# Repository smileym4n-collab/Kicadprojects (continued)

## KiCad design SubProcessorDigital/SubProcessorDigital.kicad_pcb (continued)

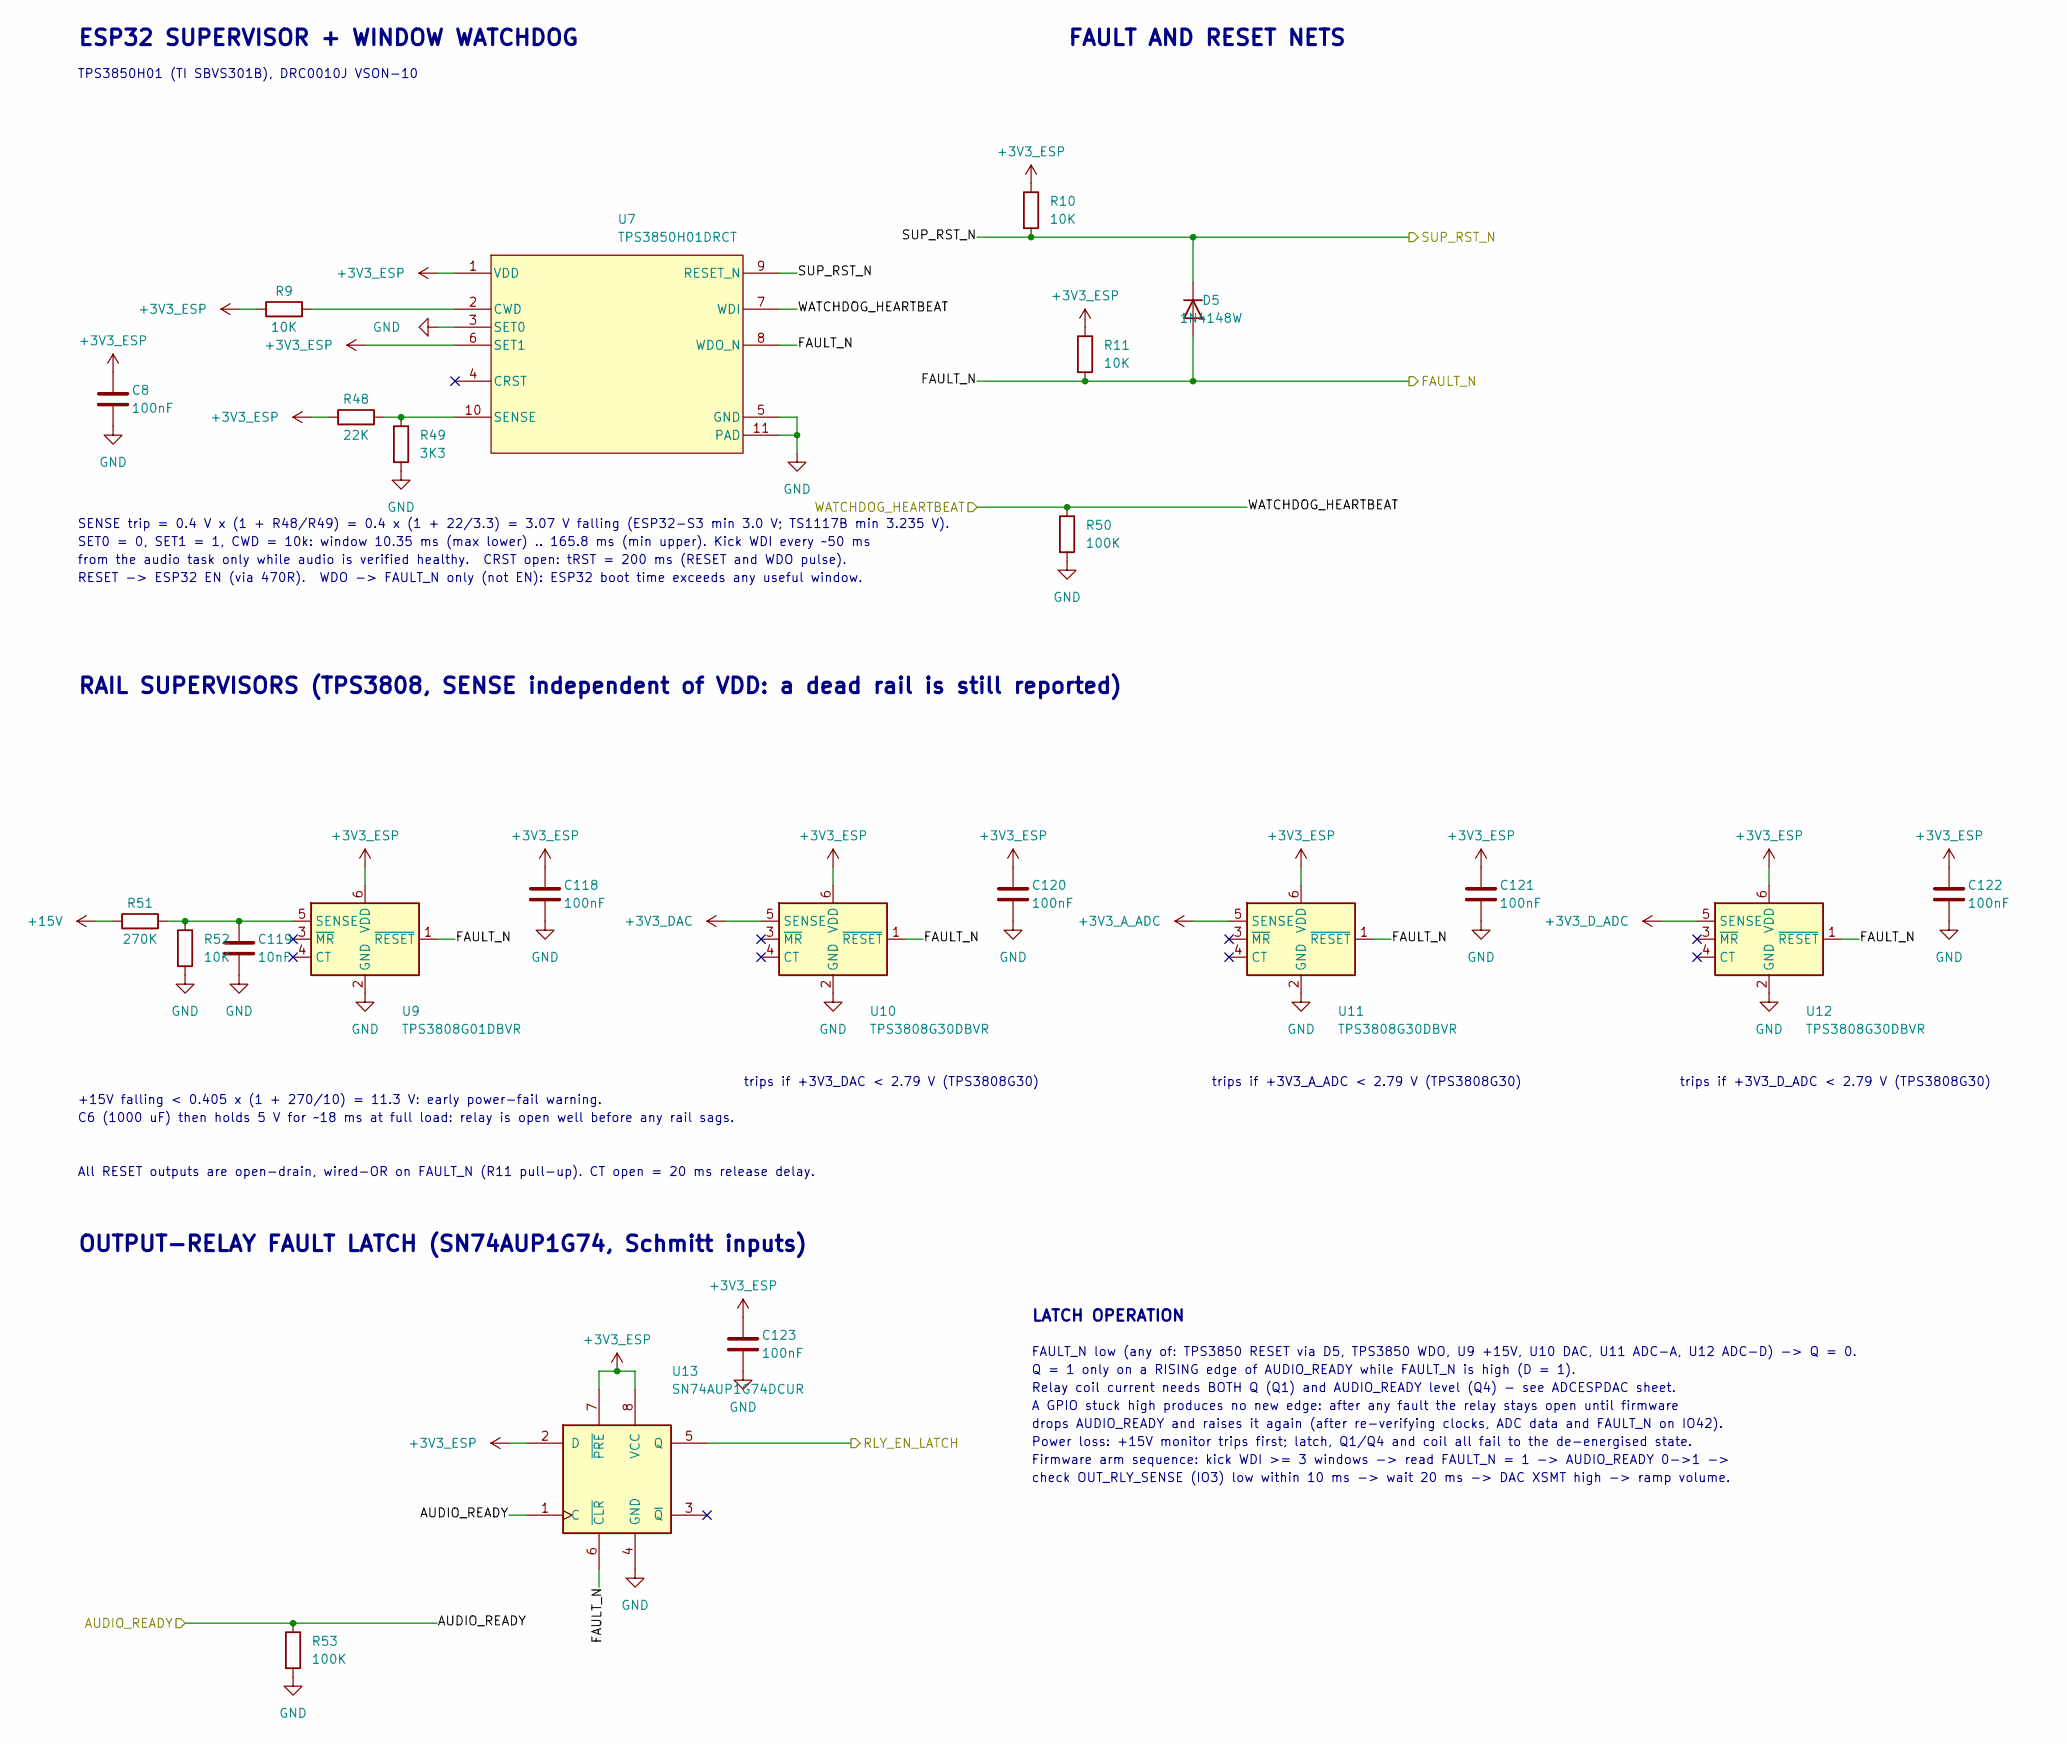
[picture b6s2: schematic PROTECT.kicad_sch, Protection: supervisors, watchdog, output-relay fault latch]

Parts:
C8, C118, C120, C121, C122, C123: 100nF; C_0603_1608Metric_Pad1.08x0.95mm_HandSolder; MPN Multicomp Pro MC0603B104K500CT (100nF 5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
C119: 10nF; C_0805_2012Metric_Pad1.18x1.45mm_HandSolder; MPN Walsin 0805B103K500CT (inventory)
D5: 1N4148W; D_SOD-123; MPN onsemi 1N4148W (inventory)
R9, R52: 10K; R_0805_2012Metric_Pad1.20x1.40mm_HandSolder; MPN 10k 0.1% thin film 2012 (inventory)
R10, R11: 10K; R_0805_2012Metric_Pad1.20x1.40mm_HandSolder; MPN KOA RK73B2ATTD103J (inventory)
R48: 22K; R_0805_2012Metric_Pad1.20x1.40mm_HandSolder; MPN Susumu RR1220P-223-D thin film 0.5% (in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
R49: 3K3; R_0805_2012Metric_Pad1.20x1.40mm_HandSolder; MPN Stackpole RMCF0805FT3K30 1% (inventory)
R50, R53: 100K; R_0805_2012Metric_Pad1.20x1.40mm_HandSolder; MPN Thick film 2012 (inventory)
R51: 270K; R_0805_2012Metric_Pad1.20x1.40mm_HandSolder; MPN 270k thick film 2012 (inventory)
U7: TPS3850H01DRCT; VSON-10-1EP_3x3mm_P0.5mm_EP1.65x2.4mm; MPN TPS3850H01DRCT
U9: TPS3808G01DBVR; SOT-23-6; MPN TPS3808G01DBVR
U10, U11, U12: TPS3808G30DBVR; SOT-23-6; MPN TPS3808G30DBVR
U13: SN74AUP1G74DCUR; VSSOP-8_2.3x2mm_P0.5mm; MPN SN74AUP1G74DCUR

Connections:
+3V3_A_ADC: U11.5 (SENSE); also elsewhere on the board
+3V3_DAC: U10.5 (SENSE); also elsewhere on the board
+3V3_D_ADC: U12.5 (SENSE); also elsewhere on the board
+3V3_ESP: C8.1, C118.1, C120.1, C121.1, C122.1, C123.1, R9.1, R10.1, R11.1, R48.1, U7.1 (VDD), U7.6 (SET1), U9.6 (VDD), U10.6 (VDD), U11.6 (VDD), U12.6 (VDD), U13.2 (D), U13.7 (~PRE), U13.8 (VCC); also elsewhere on the board
+15V: R51.1; also elsewhere on the board
/AUDIO_READY: R53.1, U13.1 (C); also elsewhere on the board
/FAULT_N: D5.2 (A), R11.2, U7.8 (WDO_N), U9.1 (~RESET), U10.1 (~RESET), U11.1 (~RESET), U12.1 (~RESET), U13.6 (~CLR); also elsewhere on the board
/RLY_EN_LATCH: U13.5 (Q); also elsewhere on the board
/SUP_RST_N: D5.1 (K), R10.2, U7.9 (RESET_N); also elsewhere on the board
/WATCHDOG_HEARTBEAT: R50.1, U7.7 (WDI); also elsewhere on the board
GND: C8.2, C118.2, C119.2, C120.2, C121.2, C122.2, C123.2, R49.2, R50.2, R52.2, R53.2, U7.3 (SET0), U7.5 (GND), U7.11 (PAD), U9.2 (GND), U10.2 (GND), U11.2 (GND), U12.2 (GND), U13.4 (GND); also elsewhere on the board
unnamed: R9.2, U7.2 (CWD)
unnamed: R48.2, R49.1, U7.10 (SENSE)
unnamed: C119.1, R51.2, R52.1, U9.5 (SENSE)

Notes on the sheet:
FAULT AND RESET NETS
ESP32 SUPERVISOR + WINDOW WATCHDOG
trips if +3V3_DAC < 2.79 V (TPS3808G30)
Relay coil current needs BOTH Q (Q1) and AUDIO_READY level (Q4) - see ADCESPDAC sheet.
Power loss: +15V monitor trips first; latch, Q1/Q4 and coil all fail to the de-energised state.
SENSE trip = 0.4 V x (1 + R48/R49) = 0.4 x (1 + 22/3.3) = 3.07 V falling (ESP32-S3 min 3.0 V; TS1117B min 3.235 V).
All RESET outputs are open-drain, wired-OR on FAULT_N (R11 pull-up). CT open = 20 ms release delay.
drops AUDIO_READY and raises it again (after re-verifying clocks, ADC data and FAULT_N on IO42).
RESET -> ESP32 EN (via 470R). WDO -> FAULT_N only (not EN): ESP32 boot time exceeds any useful window.
+15V falling < 0.405 x (1 + 270/10) = 11.3 V: early power-fail warning.
Q = 1 only on a RISING edge of AUDIO_READY while FAULT_N is high (D = 1).
Firmware arm sequence: kick WDI >= 3 windows -> read FAULT_N = 1 -> AUDIO_READY 0->1 ->
trips if +3V3_A_ADC < 2.79 V (TPS3808G30)
trips if +3V3_D_ADC < 2.79 V (TPS3808G30)
OUTPUT-RELAY FAULT LATCH (SN74AUP1G74, Schmitt inputs)
A GPIO stuck high produces no new edge: after any fault the relay stays open until firmware
TPS3850H01 (TI SBVS301B), DRC0010J VSON-10
LATCH OPERATION
from the audio task only while audio is verified healthy. CRST open: tRST = 200 ms (RESET and WDO pulse).
C6 (1000 uF) then holds 5 V for ~18 ms at full load: relay is open well before any rail sags.
check OUT_RLY_SENSE (IO3) low within 10 ms -> wait 20 ms -> DAC XSMT high -> ramp volume.
SET0 = 0, SET1 = 1, CWD = 10k: window 10.35 ms (max lower) .. 165.8 ms (min upper). Kick WDI every ~50 ms
FAULT_N low (any of: TPS3850 RESET via D5, TPS3850 WDO, U9 +15V, U10 DAC, U11 ADC-A, U12 ADC-D) -> Q = 0.
RAIL SUPERVISORS (TPS3808, SENSE independent of VDD: a dead rail is still reported)

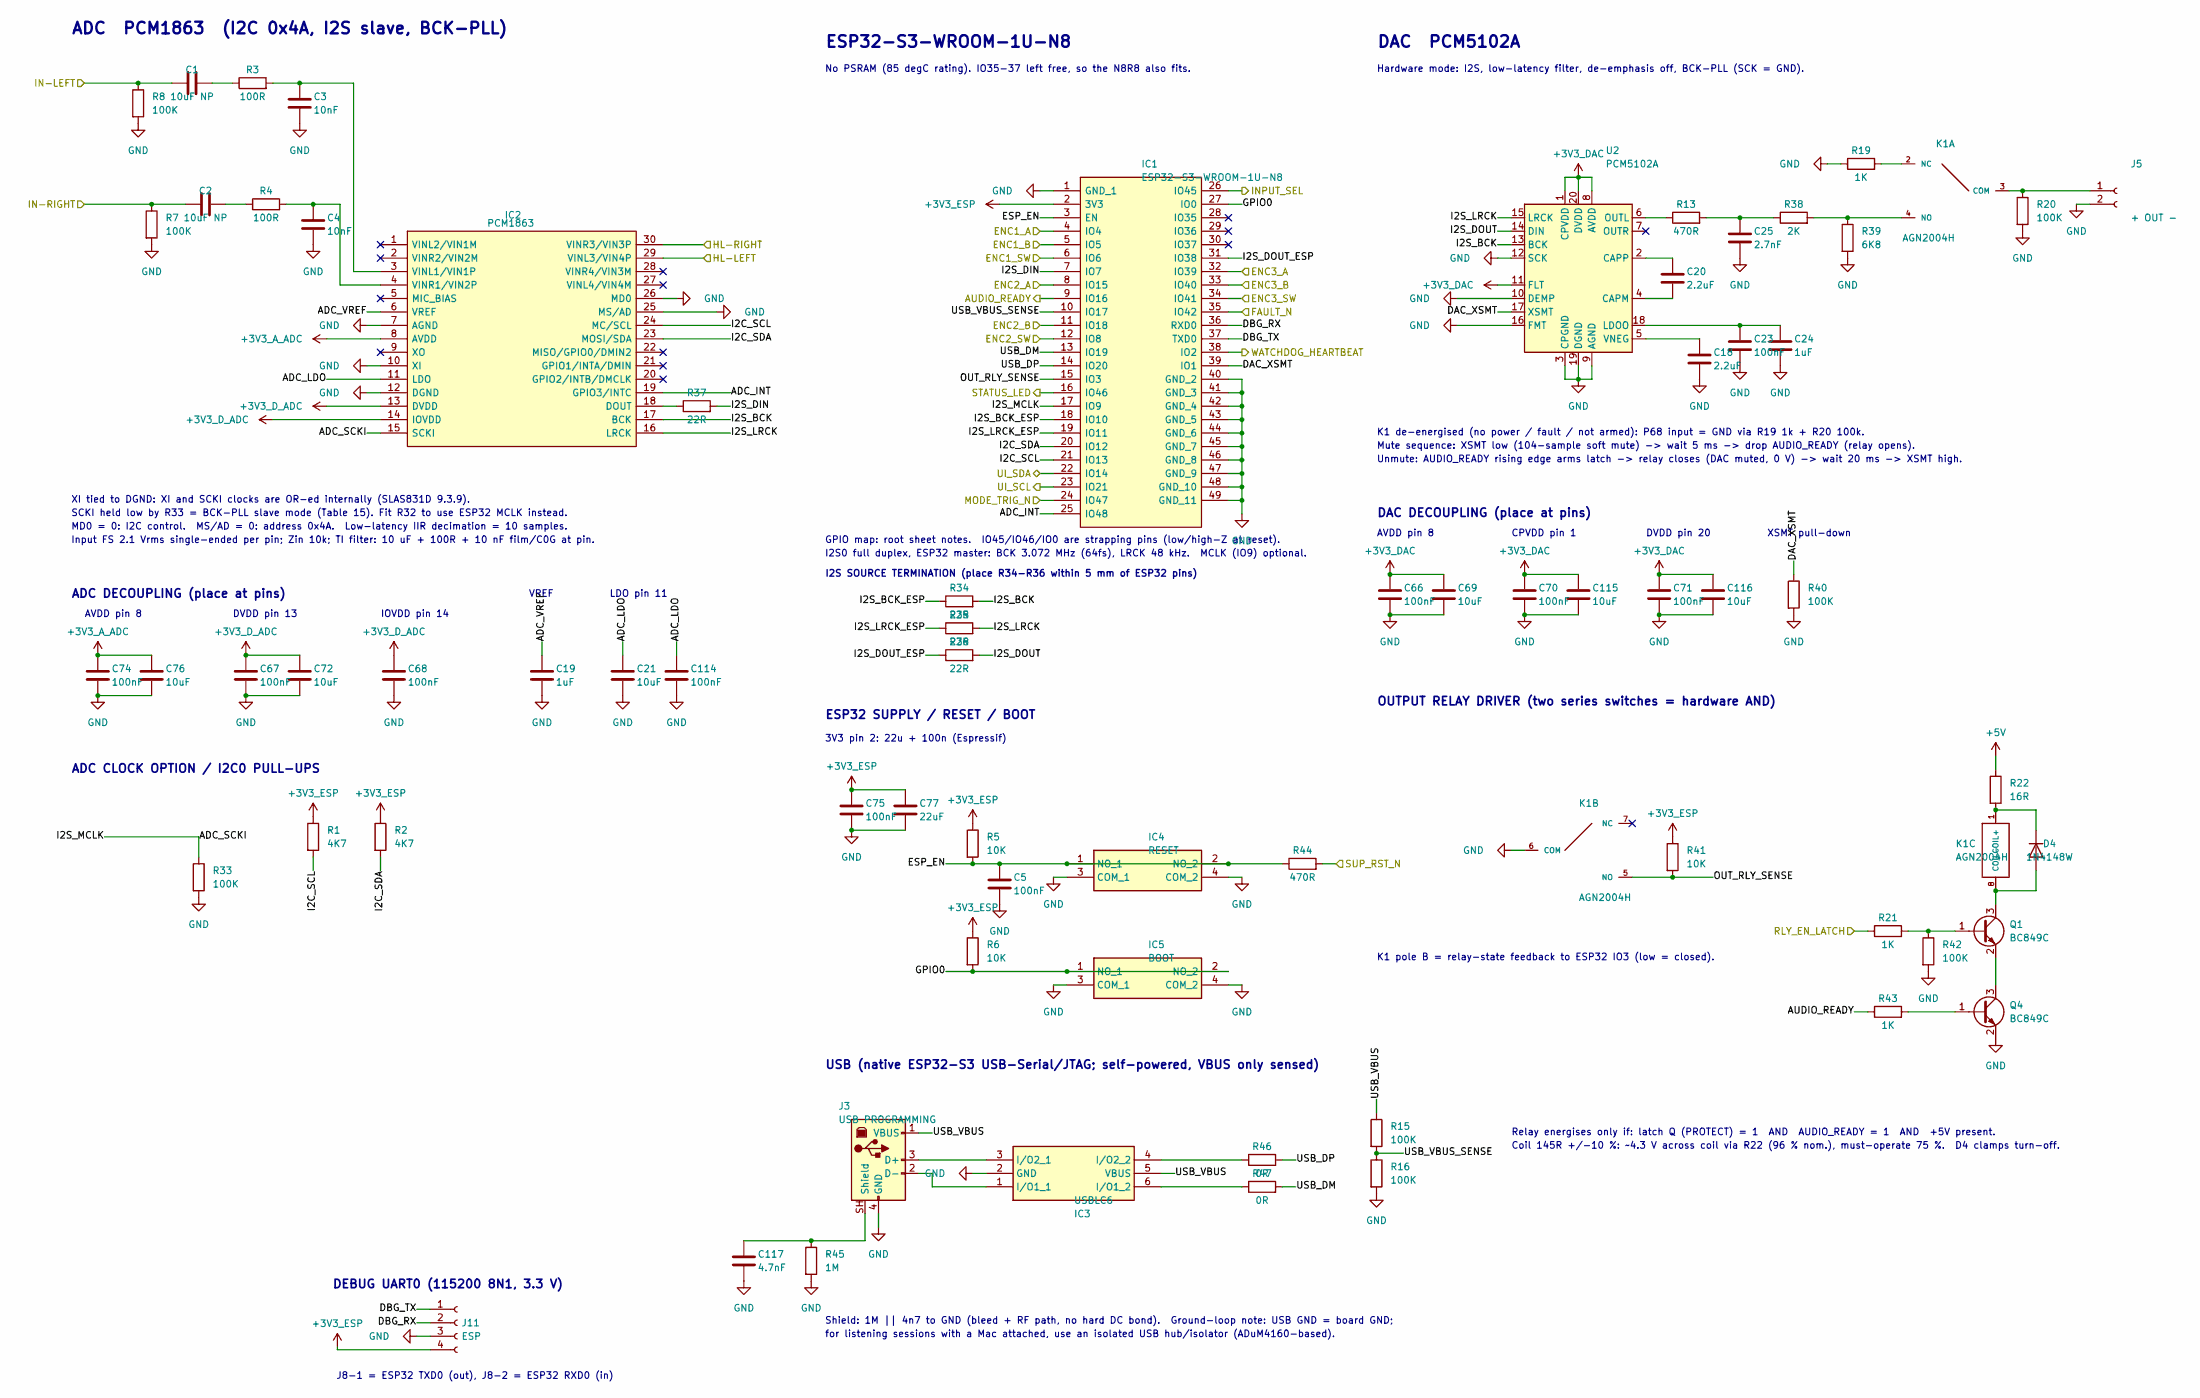
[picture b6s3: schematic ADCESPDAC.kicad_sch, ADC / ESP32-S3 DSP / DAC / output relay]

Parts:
C1, C2: 10uF NP; C_Radial_D8.0mm_H11.5mm_P3.50mm; MPN Nichicon UES1H100MPM bipolar (inventory)
C3, C4: 10nF; C_0805_2012Metric_Pad1.18x1.45mm_HandSolder; MPN Walsin 0805N103J500CT C0G (inventory)
C5, C23, C66, C67, C68, C70, C71, C74, C75, C114: 100nF; C_0603_1608Metric_Pad1.08x0.95mm_HandSolder; MPN Multicomp Pro MC0603B104K500CT (100nF 5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
C18, C20: 2.2uF; C_0805_2012Metric_Pad1.18x1.45mm_HandSolder; MPN Samsung CL21B225KPFNNNE X7R (inventory)
C19, C24: 1uF; C_1206_3216Metric_Pad1.33x1.80mm_HandSolder; MPN Samsung CL31B105KBHNFNE (inventory)
C21: 10uF; C_0805_2012Metric_Pad1.18x1.45mm_HandSolder; MPN Samsung CL21A106KOQNNNF (inventory)
C25: 2.7nF; C_0805_2012Metric_Pad1.18x1.45mm_HandSolder; MPN Walsin 0805N272J500CT C0G (inventory)
C69, C72, C76, C115, C116: 10uF; C_0805_2012Metric_Pad1.18x1.45mm_HandSolder; MPN Samsung CL21A106KOQNNNF X5R 16V (invent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
C77: 22uF; C_1206_3216Metric_Pad1.33x1.80mm_HandSolder; MPN Samsung CL31A226KAHNNNE X5R 25V (invent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
C117: 4.7nF; C_0805_2012Metric_Pad1.18x1.45mm_HandSolder; MPN Walsin 0805N472J101CT C0G 100V (invento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
D4: 1N4148W; D_SOD-123; MPN onsemi 1N4148W (inventory)
IC1: ESP32-S3-WROOM-1U-N8; ESP32S3WROOM1UN16R8; MPN ESP32-S3-WROOM-1U-N8
IC2: PCM1863; SOP50P640X120-30N; MPN PCM1863QDBTRQ1 (or PCM1863DBTR); Mouser Part Number 595-PCM1863QDBTRQ1
IC3: USBLC6; SOT-23-6; MPN STMicroelectronics USBLC6-2SC6 (invento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
IC4: RESET; TS026650BK100SCRD; MPN Same Sky TS02-66-50-BK-100-SCR-D (inven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
IC5: BOOT; TS026650BK100SCRD; MPN Same Sky TS02-66-50-BK-100-SCR-D (inven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
J3: USB PROGRAMMING; USB_B_OST_USB-B1HSxx_Horizontal; MPN On Shore USB-B1HSW6 (check vs. stocked 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
J5: + OUT -; JST_XH_B2B-XH-A_1x02_P2.50mm_Vertical; MPN JST B2B-XH-A
J11: ESP; PinSocket_1x04_P2.54mm_Vertical
K1: AGN2004H; Relay_DPDT_Panasonic_AGN2004H; MPN Panasonic AGN2004H (inventory)
Q1, Q4: BC849C; SOT-23; MPN Nexperia BC849C,215 (purchase)
R1, R2: 4K7; R_0805_2012Metric_Pad1.20x1.40mm_HandSolder; MPN Stackpole RMCF0805FT4K70 (inventory)
R3, R4: 100R; R_0805_2012Metric_Pad1.20x1.40mm_HandSolder; MPN 100R thin film 2012 (inventory)
R5, R6, R41: 10K; R_0805_2012Metric_Pad1.20x1.40mm_HandSolder; MPN KOA RK73B2ATTD103J (inventory)
R7, R8: 100K; R_0805_2012Metric_Pad1.20x1.40mm_HandSolder; MPN 100k thin film 2012 (inventory)
R13: 470R; R_0805_2012Metric_Pad1.20x1.40mm_HandSolder; MPN Susumu RR1220P-471-D thin film (invento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
R15, R16, R20, R33, R40, R42: 100K; R_0805_2012Metric_Pad1.20x1.40mm_HandSolder; MPN Thick film 2012 (inventory)
R19, R21, R43: 1K; R_0805_2012Metric_Pad1.20x1.40mm_HandSolder; MPN Thick film 2012 (inventory)
R22: 16R; R_0805_2012Metric_Pad1.20x1.40mm_HandSolder; MPN Stackpole RMCF0805FT16R0 (inventory)
R34, R35, R36, R37: 22R; R_0805_2012Metric_Pad1.20x1.40mm_HandSolder; MPN 22R thick film 2012 (inventory)
R38: 2K; R_0805_2012Metric_Pad1.20x1.40mm_HandSolder; MPN Susumu RR1220P-202-D thin film (invento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
R39: 6K8; R_0805_2012Metric_Pad1.20x1.40mm_HandSolder; MPN Susumu RR1220P-682-D thin film (invento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
R44: 470R; R_0805_2012Metric_Pad1.20x1.40mm_HandSolder; MPN Thick film 2012 (inventory)
R45: 1M; R_0805_2012Metric_Pad1.20x1.40mm_HandSolder; MPN 1M thin film 2012 (inventory)
R46, R47: 0R; R_0805_2012Metric_Pad1.20x1.40mm_HandSolder; MPN 0R 2012 (inventory)
U2: PCM5102A; TSSOP-20_4.4x6.5mm_P0.65mm; MPN PCM5102APWR

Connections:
+3V3_A_ADC: C74.1, C76.1, IC2.8 (AVDD); also elsewhere on the board
+3V3_DAC: C66.1, C69.1, C70.1, C71.1, C115.1, C116.1, U2.1 (CPVDD), U2.8 (AVDD), U2.11 (FLT), U2.20 (DVDD); also elsewhere on the board
+3V3_D_ADC: C67.1, C68.1, C72.1, IC2.13 (DVDD), IC2.14 (IOVDD); also elsewhere on the board
+3V3_ESP: C75.1, C77.1, IC1.2 (3V3), J11.4, R1.1, R2.1, R5.1, R6.1, R41.1; also elsewhere on the board
+5V: R22.1; also elsewhere on the board
/ADCESPDAC/ADC_INT: IC1.25 (IO48), IC2.19 (GPIO3/INTC)
/ADCESPDAC/ADC_LDO: C21.1, C114.1, IC2.11 (LDO)
/ADCESPDAC/ADC_SCKI: IC1.17 (IO9), IC2.15 (SCKI), R33.1
/ADCESPDAC/ADC_VREF: C19.1, IC2.6 (VREF)
/ADCESPDAC/DAC_XSMT: IC1.39 (IO1), R40.1, U2.17 (XSMT)
/ADCESPDAC/DBG_RX: IC1.36 (RXD0), J11.2
/ADCESPDAC/DBG_TX: IC1.37 (TXD0), J11.1
/ADCESPDAC/ESP_EN: C5.1, IC1.3 (EN), IC4.1 (NO_1), IC4.2 (NO_2), R5.2, R44.1
/ADCESPDAC/GPIO0: IC1.27 (IO0), IC5.1 (NO_1), IC5.2 (NO_2), R6.2
/ADCESPDAC/I2C_SCL: IC1.21 (IO13), IC2.24 (MC/SCL), R1.2
/ADCESPDAC/I2C_SDA: IC1.20 (IO12), IC2.23 (MOSI/SDA), R2.2
/ADCESPDAC/I2S_BCK: IC2.17 (BCK), R34.2, U2.13 (BCK)
/ADCESPDAC/I2S_BCK_ESP: IC1.18 (IO10), R34.1
/ADCESPDAC/I2S_DIN: IC1.7 (IO7), R37.2
/ADCESPDAC/I2S_DOUT: R36.2, U2.14 (DIN)
/ADCESPDAC/I2S_DOUT_ESP: IC1.31 (IO38), R36.1
/ADCESPDAC/I2S_LRCK: IC2.16 (LRCK), R35.2, U2.15 (LRCK)
/ADCESPDAC/I2S_LRCK_ESP: IC1.19 (IO11), R35.1
/ADCESPDAC/OUT_RLY_SENSE: IC1.15 (IO3), K1.5 (NO), R41.2
/ADCESPDAC/USB_DM: IC1.13 (IO19), R47.2
/ADCESPDAC/USB_DP: IC1.14 (IO20), R46.2
/ADCESPDAC/USB_VBUS: IC3.5 (VBUS), J3.1 (VBUS), R15.1
/ADCESPDAC/USB_VBUS_SENSE: IC1.10 (IO17), R15.2, R16.1
/AUDIO_READY: IC1.9 (IO16), R43.1; also elsewhere on the board
/ENC1_A: IC1.4 (IO4); also elsewhere on the board
/ENC1_B: IC1.5 (IO5); also elsewhere on the board
/ENC1_SW: IC1.6 (IO6); also elsewhere on the board
/ENC2_A: IC1.8 (IO15); also elsewhere on the board
/ENC2_B: IC1.11 (IO18); also elsewhere on the board
/ENC2_SW: IC1.12 (IO8); also elsewhere on the board
/ENC3_A: IC1.32 (IO39); also elsewhere on the board
/ENC3_B: IC1.33 (IO40); also elsewhere on the board
/ENC3_SW: IC1.34 (IO41); also elsewhere on the board
/FAULT_N: IC1.35 (IO42); also elsewhere on the board
/HL-LEFT: IC2.29 (VINL3/VIN4P); also elsewhere on the board
/HL-RIGHT: IC2.30 (VINR3/VIN3P); also elsewhere on the board
/IN-LEFT: C1.1, R8.1; also elsewhere on the board
/IN-RIGHT: C2.1, R7.1; also elsewhere on the board
/INPUT_SEL: IC1.26 (IO45); also elsewhere on the board
/MODE_TRIG_N: IC1.24 (IO47); also elsewhere on the board
/RLY_EN_LATCH: R21.1; also elsewhere on the board
/STATUS_LED: IC1.16 (IO46); also elsewhere on the board
/SUP_RST_N: R44.2; also elsewhere on the board
/UI_SCL: IC1.23 (IO21); also elsewhere on the board
/UI_SDA: IC1.22 (IO14); also elsewhere on the board
/WATCHDOG_HEARTBEAT: IC1.38 (IO2); also elsewhere on the board
GND: C3.2, C4.2, C5.2, C18.2, C19.2, C21.2, C23.2, C24.2, C25.2, C66.2, C67.2, C68.2, C69.2, C70.2, C71.2, C72.2, C74.2, C75.2, C76.2, C77.2, C114.2, C115.2, C116.2, C117.2, IC1.1 (GND_1), IC1.40 (GND_2), IC1.41 (GND_3), IC1.42 (GND_4), IC1.43 (GND_5), IC1.44 (GND_6), IC1.45 (GND_7), IC1.46 (GND_8), IC1.47 (GND_9), IC1.48 (GND_10), IC1.49 (GND_11), IC2.7 (AGND), IC2.10 (XI), IC2.12 (DGND), IC2.25 (MS/AD), IC2.26 (MD0), IC3.2 (GND), IC4.3 (COM_1), IC4.4 (COM_2), IC5.3 (COM_1), IC5.4 (COM_2), J3.4 (GND), J5.2, J11.3, K1.6 (COM), Q4.2 (E), R7.2, R8.2, R16.2, R19.1, R20.2, R33.2, R39.2, R40.2, R42.2, R45.2, U2.3 (CPGND), U2.9 (AGND), U2.10 (DEMP), U2.12 (SCK), U2.16 (FMT), U2.19 (DGND); also elsewhere on the board
unnamed: C1.2, R3.1
unnamed: C2.2, R4.1
unnamed: C25.1, R13.2, R38.1
unnamed: D4.2 (A), K1.8 (COIL-), Q1.3 (C)
unnamed: D4.1 (K), K1.1 (COIL+), R22.2
unnamed: IC2.18 (DOUT), R37.1
unnamed: C3.1, IC2.3 (VINL1/VIN1P), R3.2
unnamed: C4.1, IC2.4 (VINR1/VIN2P), R4.2
unnamed: IC3.1 (I/O1_1), J3.2 (D-)
unnamed: IC3.6 (I/O1_2), R47.1
unnamed: IC3.3 (I/O2_1), J3.3 (D+)
unnamed: IC3.4 (I/O2_2), R46.1
unnamed: C117.1, J3.SH (Shield), R45.1
unnamed: J5.1, K1.3 (COM), R20.1
unnamed: K1.2 (NC), R19.2
unnamed: K1.4 (NO), R38.2, R39.1
unnamed: Q1.1 (B), R21.2, R42.1
unnamed: Q1.2 (E), Q4.3 (C)
unnamed: Q4.1 (B), R43.2
unnamed: C20.2, U2.4 (CAPM)
unnamed: C20.1, U2.2 (CAPP)
unnamed: C23.1, C24.1, U2.18 (LDOO)
unnamed: R13.1, U2.6 (OUTL)
unnamed: C18.1, U2.5 (VNEG)

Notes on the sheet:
Unmute: AUDIO_READY rising edge arms latch -> relay closes (DAC muted, 0 V) -> wait 20 ms -> XSMT high.
ADC DECOUPLING (place at pins)
IOVDD pin 14
VREF
Mute sequence: XSMT low (104-sample soft mute) -> wait 5 ms -> drop AUDIO_READY (relay opens).
XSMT pull-down
USB (native ESP32-S3 USB-Serial/JTAG; self-powered, VBUS only sensed)
SCKI held low by R33 = BCK-PLL slave mode (Table 15). Fit R32 to use ESP32 MCLK instead.
Relay energises only if: latch Q (PROTECT) = 1 AND AUDIO_READY = 1 AND +5V present.
Coil 145R +/-10 %: ~4.3 V across coil via R22 (96 % nom.), must-operate 75 %. D4 clamps turn-off.
OUTPUT RELAY DRIVER (two series switches = hardware AND)
CPVDD pin 1
Shield: 1M || 4n7 to GND (bleed + RF path, no hard DC bond). Ground-loop note: USB GND = board GND;
AVDD pin 8
DEBUG UART0 (115200 8N1, 3.3 V)
GPIO map: root sheet notes. IO45/IO46/IO0 are strapping pins (low/high-Z at reset).
ESP32-S3-WROOM-1U-N8
ESP32 SUPPLY / RESET / BOOT
K1 pole B = relay-state feedback to ESP32 IO3 (low = closed).
ADC PCM1863 (I2C 0x4A, I2S slave, BCK-PLL)
XI tied to DGND: XI and SCKI clocks are OR-ed internally (SLAS831D 9.3.9).
Hardware mode: I2S, low-latency filter, de-emphasis off, BCK-PLL (SCK = GND).
I2S SOURCE TERMINATION (place R34-R36 within 5 mm of ESP32 pins)
I2S0 full duplex, ESP32 master: BCK 3.072 MHz (64fs), LRCK 48 kHz. MCLK (IO9) optional.
DVDD pin 13
MD0 = 0: I2C control. MS/AD = 0: address 0x4A. Low-latency IIR decimation = 10 samples.
No PSRAM (85 degC rating). IO35-37 left free, so the N8R8 also fits.
K1 de-energised (no power / fault / not armed): P68 input = GND via R19 1k + R20 100k.
LDO pin 11
J8-1 = ESP32 TXD0 (out), J8-2 = ESP32 RXD0 (in)
DAC DECOUPLING (place at pins)
Input FS 2.1 Vrms single-ended per pin; Zin 10k; TI filter: 10 uF + 100R + 10 nF film/C0G at pin.
DVDD pin 20
for listening sessions with a Mac attached, use an isolated USB hub/isolator (ADuM4160-based).
DAC PCM5102A
3V3 pin 2: 22u + 100n (Espressif)
ADC CLOCK OPTION / I2C0 PULL-UPS

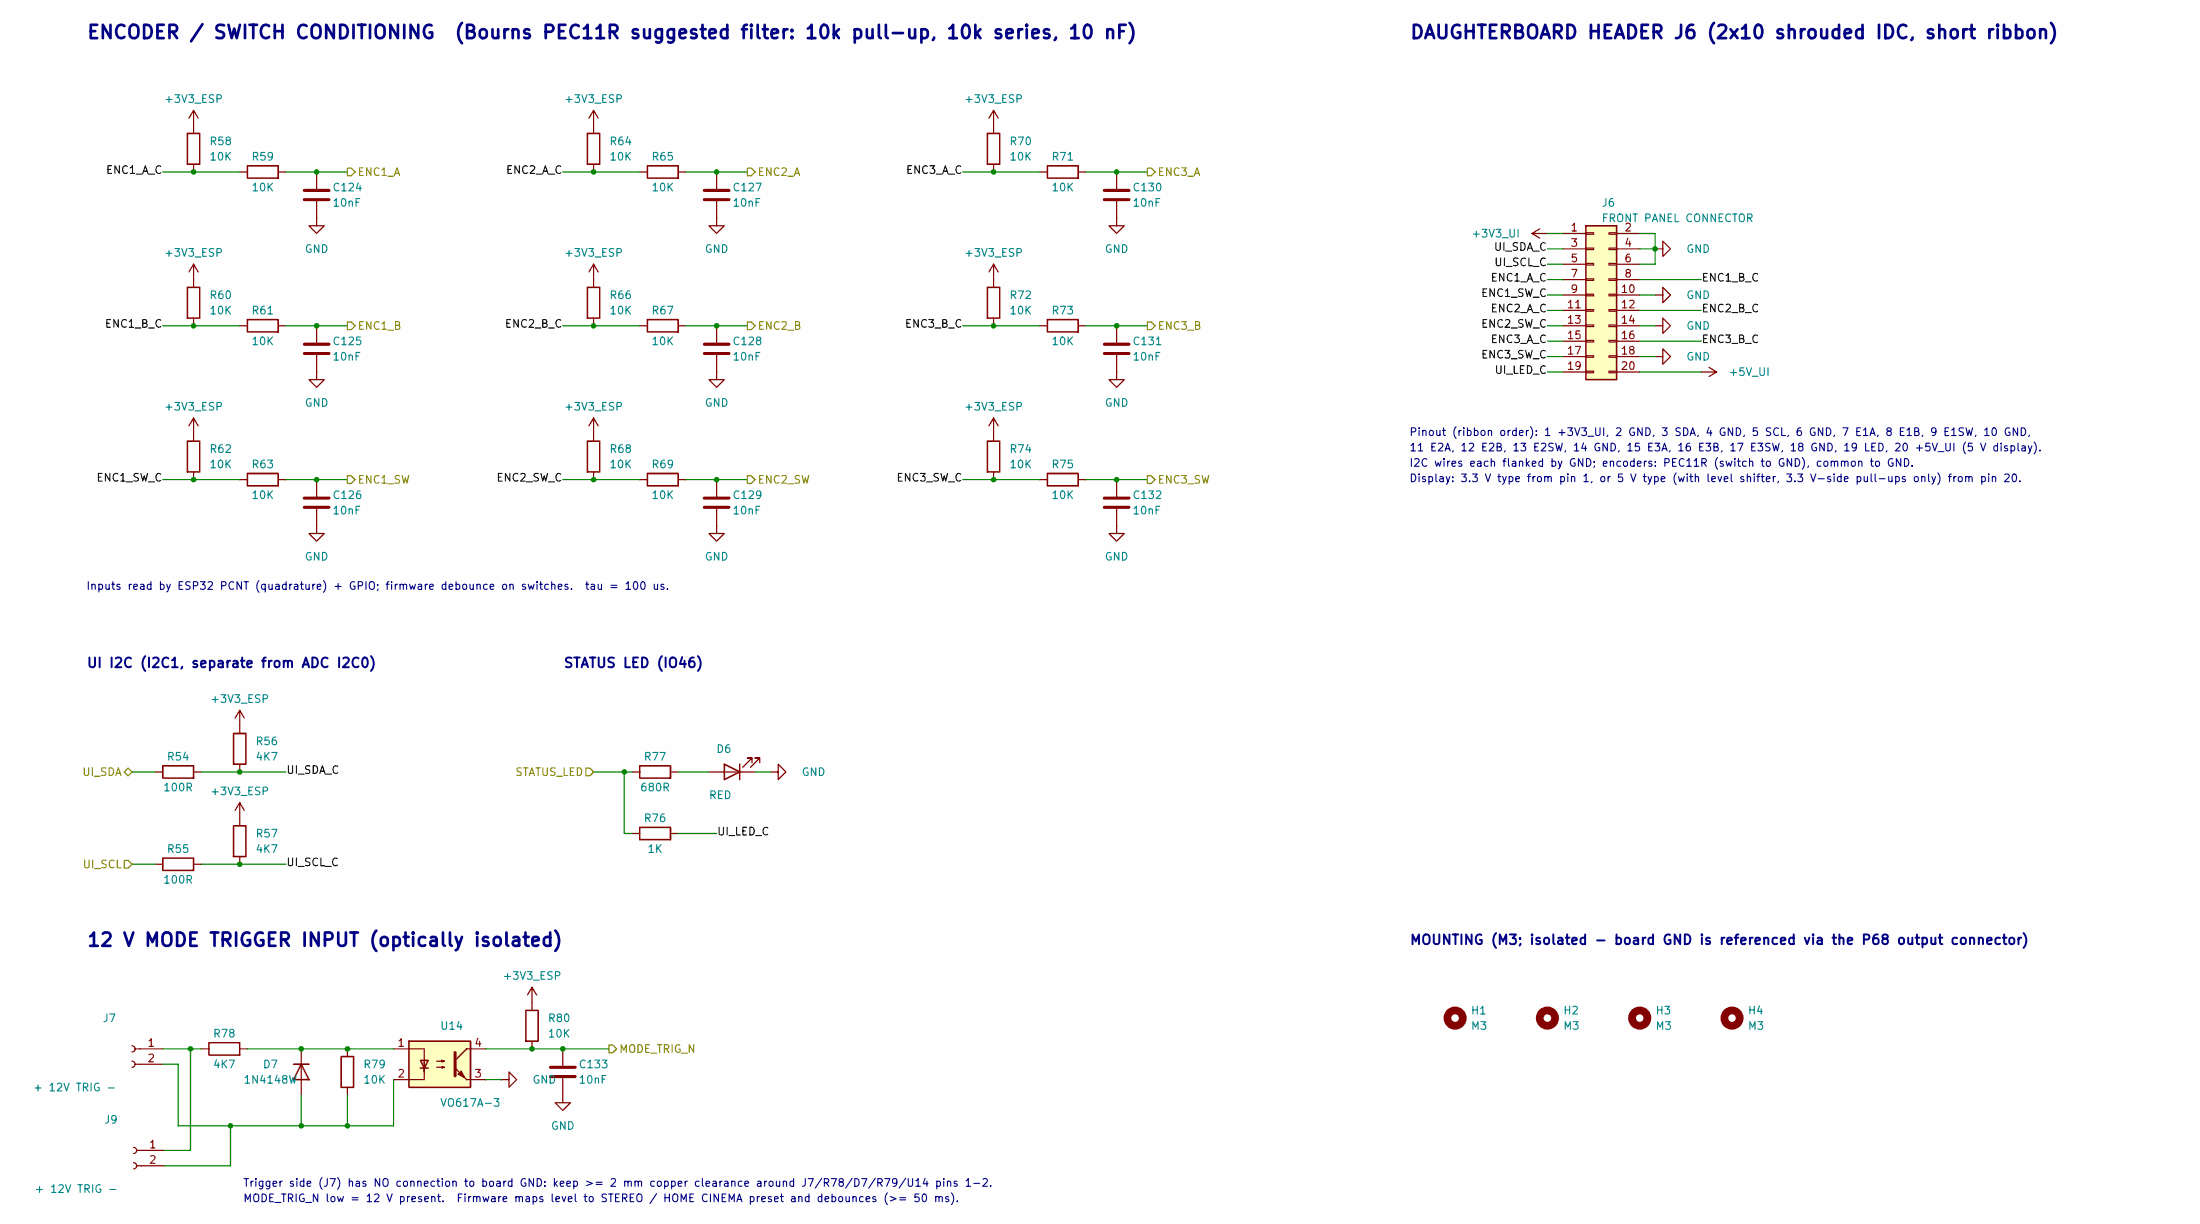
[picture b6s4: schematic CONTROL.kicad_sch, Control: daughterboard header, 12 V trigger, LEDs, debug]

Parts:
C124, C125, C126, C127, C128, C129, C130, C131, C132, C133: 10nF; C_0805_2012Metric_Pad1.18x1.45mm_HandSolder; MPN Walsin 0805N103J500CT (inventory)
D6: RED; LED_0805_2012Metric_Pad1.15x1.40mm_HandSolder; MPN Kingbright KP-2012EC (inventory)
D7: 1N4148W; D_SOD-123; MPN onsemi 1N4148W (inventory)
H1, H2, H3, H4: M3; MountingHole_3.2mm_M3
J6: FRONT PANEL CONNECTOR; IDC-Header_2x10_P2.54mm_Vertical; MPN Shrouded box header 2x10 2.54 mm, e.g. 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
J7, J9: + 12V TRIG -; JST_XH_B2B-XH-A_1x02_P2.50mm_Vertical; MPN JST B2B-XH-A
R54, R55: 100R; R_0805_2012Metric_Pad1.20x1.40mm_HandSolder; MPN 100R thick film 2012 (inventory)
R56, R57: 4K7; R_0805_2012Metric_Pad1.20x1.40mm_HandSolder; MPN Stackpole RMCF0805FT4K70 (inventory)
R58, R59, R60, R61, R62, R63, R64, R65, R66, R67, R68, R69, R70, R71, R72, R73, R74, R75, R79, R80: 10K; R_0805_2012Metric_Pad1.20x1.40mm_HandSolder; MPN KOA RK73B2ATTD103J (inventory)
R76: 1K; R_0805_2012Metric_Pad1.20x1.40mm_HandSolder; MPN Thick film 2012 (inventory)
R77: 680R; R_0805_2012Metric_Pad1.20x1.40mm_HandSolder; MPN 680R thin film 2012 (inventory)
R78: 4K7; R_0805_2012Metric_Pad1.20x1.40mm_HandSolder; MPN Stackpole RMCF0805FT4K70 125 mW (invent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
U14: VO617A-3; DIP-4_W7.62mm; MPN Vishay VO617A-3

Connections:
+3V3_ESP: R56.1, R57.1, R58.1, R60.1, R62.1, R64.1, R66.1, R68.1, R70.1, R72.1, R74.1, R80.1; also elsewhere on the board
+3V3_UI: J6.1; also elsewhere on the board
+5V_UI: J6.20; also elsewhere on the board
/CONTROL/ENC1_A_C: J6.7, R58.2, R59.1
/CONTROL/ENC1_B_C: J6.8, R60.2, R61.1
/CONTROL/ENC1_SW_C: J6.9, R62.2, R63.1
/CONTROL/ENC2_A_C: J6.11, R64.2, R65.1
/CONTROL/ENC2_B_C: J6.12, R66.2, R67.1
/CONTROL/ENC2_SW_C: J6.13, R68.2, R69.1
/CONTROL/ENC3_A_C: J6.15, R70.2, R71.1
/CONTROL/ENC3_B_C: J6.16, R72.2, R73.1
/CONTROL/ENC3_SW_C: J6.17, R74.2, R75.1
/CONTROL/UI_LED_C: J6.19, R76.2
/CONTROL/UI_SCL_C: J6.5, R55.2, R57.2
/CONTROL/UI_SDA_C: J6.3, R54.2, R56.2
/ENC1_A: C124.1, R59.2; also elsewhere on the board
/ENC1_B: C125.1, R61.2; also elsewhere on the board
/ENC1_SW: C126.1, R63.2; also elsewhere on the board
/ENC2_A: C127.1, R65.2; also elsewhere on the board
/ENC2_B: C128.1, R67.2; also elsewhere on the board
/ENC2_SW: C129.1, R69.2; also elsewhere on the board
/ENC3_A: C130.1, R71.2; also elsewhere on the board
/ENC3_B: C131.1, R73.2; also elsewhere on the board
/ENC3_SW: C132.1, R75.2; also elsewhere on the board
/MODE_TRIG_N: C133.1, R80.2, U14.4; also elsewhere on the board
/STATUS_LED: R76.1, R77.1; also elsewhere on the board
/UI_SCL: R55.1; also elsewhere on the board
/UI_SDA: R54.1; also elsewhere on the board
GND: C124.2, C125.2, C126.2, C127.2, C128.2, C129.2, C130.2, C131.2, C132.2, C133.2, D6.1 (K), J6.2, J6.4, J6.6, J6.10, J6.14, J6.18, U14.3; also elsewhere on the board
unnamed: D6.2 (A), R77.2
unnamed: D7.2 (A), J7.2, J9.2, R79.2, U14.2
unnamed: D7.1 (K), R78.2, R79.1, U14.1
unnamed: J7.1, J9.1, R78.1

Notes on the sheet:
STATUS LED (IO46)
DAUGHTERBOARD HEADER J6 (2x10 shrouded IDC, short ribbon)
Pinout (ribbon order): 1 +3V3_UI, 2 GND, 3 SDA, 4 GND, 5 SCL, 6 GND, 7 E1A, 8 E1B, 9 E1SW, 10 GND,
12 V MODE TRIGGER INPUT (optically isolated)
Trigger side (J7) has NO connection to board GND: keep >= 2 mm copper clearance around J7/R78/D7/R79/U14 pins 1-2.
I2C wires each flanked by GND; encoders: PEC11R (switch to GND), common to GND.
MODE_TRIG_N low = 12 V present. Firmware maps level to STEREO / HOME CINEMA preset and debounces (>= 50 ms).
ENCODER / SWITCH CONDITIONING (Bourns PEC11R suggested filter: 10k pull-up, 10k series, 10 nF)
UI I2C (I2C1, separate from ADC I2C0)
Display: 3.3 V type from pin 1, or 5 V type (with level shifter, 3.3 V-side pull-ups only) from pin 20.
MOUNTING (M3; isolated - board GND is referenced via the P68 output connector)
11 E2A, 12 E2B, 13 E2SW, 14 GND, 15 E3A, 16 E3B, 17 E3SW, 18 GND, 19 LED, 20 +5V_UI (5 V display).
Inputs read by ESP32 PCNT (quadrature) + GPIO; firmware debounce on switches. tau = 100 us.
